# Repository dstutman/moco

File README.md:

# MoCo

Moco is a closed-loop brushless-motor controller. It is meant to glom onto the back of a 2805 gimbal motor and provide precise torque, speed, and position control.

## Versioning
Versioning is in vArB format. Incrementing B indicates a new revision has been produced that does not change external interfaces (form factor, communications, etc...). Incrementing A indicates a new version that changes these external interfaces. Until version 1 no there are no stability guarauntees.

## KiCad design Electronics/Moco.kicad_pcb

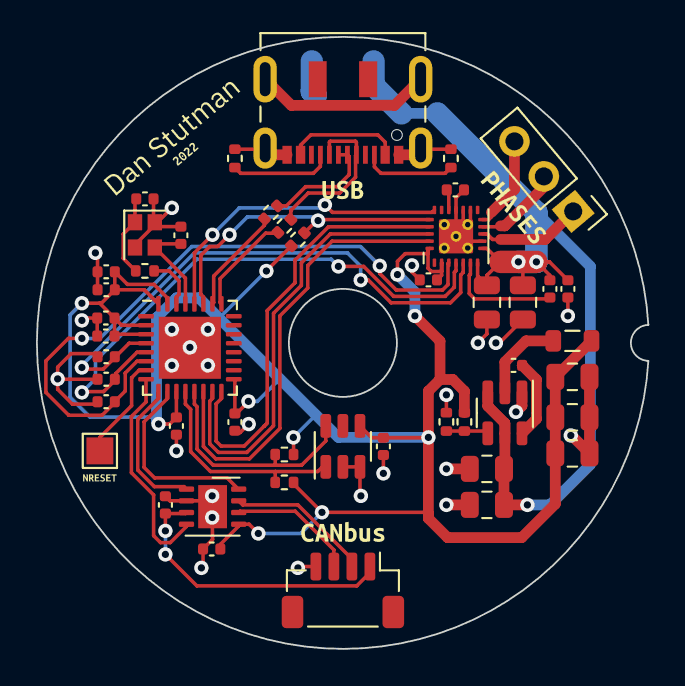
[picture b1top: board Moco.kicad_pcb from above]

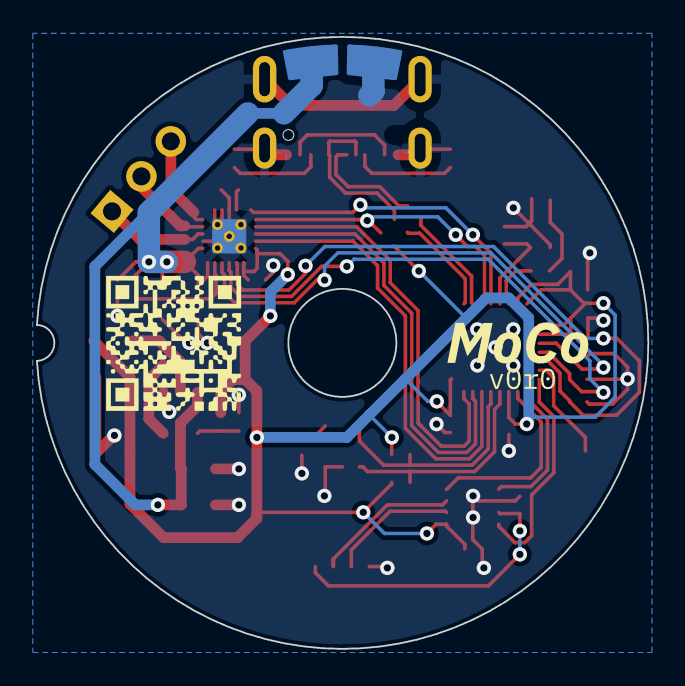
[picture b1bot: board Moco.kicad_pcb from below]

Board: 2 copper layers, 34.0 x 34.0 mm, 57 parts (4 on the bottom side), 37 nets.

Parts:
C1, C10: 1uF 6.3V; C_0402_1005Metric
C5: 0.1uF 10V; C_0402_1005Metric
C7: 0.1uF 6.3V X7R; C_0402_1005Metric
C8: 0.1uF 25V; C_0402_1005Metric
C9, C12, C14, C17, C21, C22, C23, C24, C25: 0.1uF 6.3V; C_0402_1005Metric
C11: 0.1uF VBUS; C_0402_1005Metric
C13, C15: 10uF VBUS; C_0805_2012Metric
C18: 10nF 6.3V; C_0402_1005Metric
C19, C20: XpF 6.3V; C_0402_1005Metric
C26, C27: 10uF 25V; C_0805_2012Metric
C28: 0.1uF; C_0402_1005Metric
C29, C30, C31: 22uF 6.3V; C_0805_2012Metric
J3: USB_C_Receptacle_USB2.0; USB_C_Receptacle_JAE_DX07S016JA1R1500
J4: Conn_01x03; PinHeader_1x03_P2.54mm_Vertical
J6: Conn_01x04; JST_SH_BM04B-SRSS-TB_1x04-1MP_P1.00mm_Vertical
J8, J9: Conn_01x01; Pad_CircularEdge_Ro16.5Ri15_Single
L2: 3.3uH 750mA; L_0805_2012Metric
R1, R2: 910R; R_0402_1005Metric
R4: 10 kR; R_0402_1005Metric
R5: 100R; R_0402_1005Metric
R6: 33.2kR; R_0402_1005Metric
R7: 10kR; R_0402_1005Metric
R8, R9: 5.1kR; R_0402_1005Metric
R10, R11: 22R; R_0402_1005Metric
TP1: TestPoint; TestPoint_Pad_1.5x1.5mm
U1: ESP32-C3; QFN-32-1EP_5x5mm_P0.5mm_EP3.45x3.45mm
U2: TPS562201; SOT-23-6
U3: TMAG5273; SOT-23-6
U4: DRV8311
U5: TJA1462ATK/0Z; HVSON-8-1EP_3x3mm_P0.65mm_EP1.6x2.4mm
Y1: 40 MHz +-10ppm; Crystal_SMD_2016-4Pin_2.0x1.6mm
kibuzzard-624C491C: G***; kibuzzard-624C491C
kibuzzard-626ED451: G***; kibuzzard-626ED451
kibuzzard-626ED465: G***; kibuzzard-626ED465
kibuzzard-626ED487: G***; kibuzzard-626ED487
kibuzzard-627B83F7: G***; kibuzzard-627B83F7
kibuzzard-6244CA09: G***; kibuzzard-6244CA09
kibuzzard-6244D452: G***; kibuzzard-6244D452
kibuzzard-62725C85: G***; kibuzzard-62725C85

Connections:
+3V3: C1.1, C7.2, C9.1, C12.1, C18.1, C21.1, C22.1, C23.1, C24.1, C29.2, C30.2, C31.2, L2.2, R1.2, R2.1, R4.1, R6.1, U1.2 (VDD3P3), U1.3 (VDD3P3), U1.11 (VDD3P3_RTC), U1.17 (VDD3P3_CPU), U1.31 (VDDA), U1.32 (VDDA), U3.4 (VCC), U4.2 (CSAREF), U4.24 (~SLEEP), U5.5 (VIO)
+5V: C5.1, J6.1, U5.3 (VCC)
/CANH: J6.2, U5.7 (CANH)
/CANL: J6.3, U5.6 (CANL)
/CAN_EN: U1.10 (MTDI/GPIO5/ADC2_CH0), U5.8 (STB)
/CAN_RX: U1.8 (GPIO3/ADC1_CH3), U5.4 (RXD)
/CAN_TX: U1.9 (MTMS/GPIO4/ADC1_CH4), U5.1 (TXD)
/DRV_~SCS: R4.2, U1.27 (U0RXD/GPIO20), U4.20 (~SCS)
/PWM_SYNC: U1.28 (U0TXD/GPIO21), U4.19 (PWM_SYNC)
/SCLK: U1.14 (GPIO8), U4.23 (SCLK)
/SDI: U1.15 (GPIO9/BOOT), U4.22 (SDI)
/SDO: U1.16 (GPIO10), U4.21 (SDO)
/SOA: C14.1, U1.4 (XTAL_32K_P/ADC1_CH0), U4.5 (SOA)
/SOB: C17.2, U1.5 (XTAL_32K_N/ADC1_CH1), U4.4 (SOB)
/SOC: C25.2, U1.6 (GPIO2/ADC1_CH2), U4.3 (SOC)
/TMS_SCL: R2.2, U1.12 (MTCK/GPIO6), U3.1 (SCL)
/TMS_SDA: R1.1, U1.13 (MTDO/GPIO7), U3.6 (SDA)
/USB_CONN_DN: J3.A7 (D-), J3.B7 (D-), R10.2
/USB_CONN_DP: J3.A6 (D+), J3.B6 (D+), R11.2
/USB_DN: R10.1, U1.25 (GPIO18/USB_D-)
/USB_DP: R11.1, U1.26 (GPIO19/USB_D+)
/~RESET: TP1.1, U1.7 (CHIP_EN)
GND: C1.2, C5.2, C7.1, C9.2, C10.2, C11.2, C12.2, C13.2, C14.2, C15.2, C17.1, C18.2, C19.2, C20.2, C21.2, C22.2, C23.2, C24.2, C25.1, C26.2, C27.2, C29.1, C30.1, C31.1, J3.A1 (GND), J3.A12 (GND), J3.B1 (GND), J3.B12 (GND), J3.S1 (SHIELD), J6.4, J9.1, R7.2, R8.1, R9.1, U1.33 (GND), U2.1 (GND), U3.2 (GND), U3.3 (TEST), U4.9 (PGND), U4.14 (AD1), U4.15 (AD0), U4.16 (AGND), U4.25 (PGND), U5.2 (GND), U5.9 (GND), Y1.2, Y1.4
unnamed: C8.2, U4.6 (CP)
unnamed: C10.1, U4.17 (AVDD)
unnamed: C19.1, U1.29 (XTAL_N), Y1.3
unnamed: C20.1, R5.1, Y1.1
unnamed: C28.1, L2.1, U2.2 (SW)
unnamed: C28.2, U2.6 (VBST)
unnamed: J3.A5 (CC1), R8.2
unnamed: J3.B5 (CC2), R9.2
unnamed: J4.1, U4.10 (OUTA)
unnamed: J4.2, U4.11 (OUTB)
unnamed: J4.3, U4.12 (OUTC)
unnamed: R5.2, U1.30 (XTAL_P)
unnamed: R6.2, R7.1, U2.4 (VFB)
Vdrive: C8.1, C11.1, C13.1, C15.1, C26.1, C27.1, J8.1, U2.3 (VIN), U2.5 (EN), U4.7 (VIN_AVDD), U4.8 (VM)

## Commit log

2022-04-05 Add checklist
2022-04-05 Update checklist with results of thermal simulation
2022-04-05 Add KiCAD outputs to gitignore
2022-04-05 Trade nFAULT for nSCS to avoid power on indeterminacy
2022-04-05 Update versioning scheme
2022-04-05 Remove spurious round-tracks-config
2022-04-25 Update silk (I think)
    I am not entirely sure what changes are in this commit. I think it is mostly
    just silk modifications.
2022-04-25 Switch from EFM32PG22 to EFR32BG22
    The EFM32PG22 is not currently available. The EFR32BG22 is downwards
    pin-for-pin compatible with it so I'll use that instead (for now).
2022-04-25 Update EFR32 part number
2022-04-25 Improve decoupling
2022-05-01 New design with ESP32-C3
    This design swaps the EFM32PG22 for an ESP32-C3. This reduces cost
    and improves availability. It also lets me use USB and CANbus instead
    of RS485.
2022-05-04 Complete ESP32-C3 redesign
    - Remove status LED to free up pin
    - Avoid using embedded flash SPI pins
    - Update silkscreen
    - Improve I2C and CANbus pin assignments
2022-05-04 Remove unused checklist
2022-05-04 Remove duplicate library folder
2022-05-11 Correct I2C net labels, add NRESET pad
2022-06-13 Add Firmware directory
    `main.rs` temporarily excluded.
2022-06-13 Add asynchronous executor
2022-06-13 Add I2C driver
    Unverified, probably doesn't work yet
